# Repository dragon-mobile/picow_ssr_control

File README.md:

# picow_ssr_control

<br/>

<br/>

The Raspberry Pi Pico W Solid State Relay Controller is primarily meant to be
used with an open hardware solid state relay PCBs that is being co-developed
alongside this project as part of my Dragon Mobile GitHub organization to make
useful hardware with associated firmware and software for the tiny home, van
life and maker communities.

## Contributing

Contributors are welcome.
Please note that this project has a [Contributor Covenant Code of Conduct].
By participating in this project you agree to abide by its terms.

All intentionally contributed hardware will be considered to be contributed
under the [CERN] license without any additional terms or conditions.

All intentionally contributed code will be considered to be contributed
under a [MIT] license without any additional terms or conditions.
Please include your information in a comment on all code files for the copyright
etc.

All intentionally contributed documentation, CAD files and libraries, footprints,
artwork or non-code text like this README etc. will be considered to be
contributed under the same [CC-BY-SA] license without any additional terms or
conditions.

Pull requests are always welcome. For major changes, please open an issue first
to discuss what you would like to change.
Please make sure to update or add tests as appropriate for all software changes.

## Licenses

<br/>

All hardware is licensed under the

  * [CERN] - CERN-OHL-W-2.0
  
You can find a copy of the CERN Open Hardware License - Weakly-reciprocal v2.0
in the [LICENSE-CERN-OHL-W-2] file and the how-to guide in the
[CERN-HOWTO_GUIDE] file.

All code is licensed under the

  * [MIT] - MIT License

You can find a copy of the license in the [LICENSE-MIT] file.

All documentation like this README is licensed under the Creative Commons
Attribution-ShareAlike 4.0 International License (CC-BY-SA).

All original CAD files and libraries, footprints, and artwork are also licensed
under the
Creative Commons Attribution-ShareAlike 4.0 International License (CC-BY-SA).
You can find a copy of the [CC-BY-SA] license in the [LICENSE-CC-BY-SA] file.

If after reading the above license files, how-tos, and related FAQs on the
linked license sites on how they apply to the project please either open an
issue or contact me (Michael Cummings) via my Github email and I will try
to guided you through my understanding of how it works.

[CC-BY-SA]: http://creativecommons.org/licenses/by-sa/4.0/
[CERN]: https://ohwr.org/project/cernohl/wikis/Documents/CERN-OHL-version-2
[CERN-HOWTO_GUIDE]: docs/cern_ohl_w_v2_howto.pdf
[Contributor Covenant Code of Conduct]: CODE_OF_CONDUCT.md 
[LICENSE-CC-BY-SA]: LICENSE-CC-BY-SA
[LICENSE-CERN-OHL-W-2]: CERN-OHL-W-2
[LICENSE-MIT]: LICENSE-MIT
[MIT]: https://opensource.org/licenses/MIT

<hr>
Copyright &copy; 2022-2023, Michael Cummings<br/>

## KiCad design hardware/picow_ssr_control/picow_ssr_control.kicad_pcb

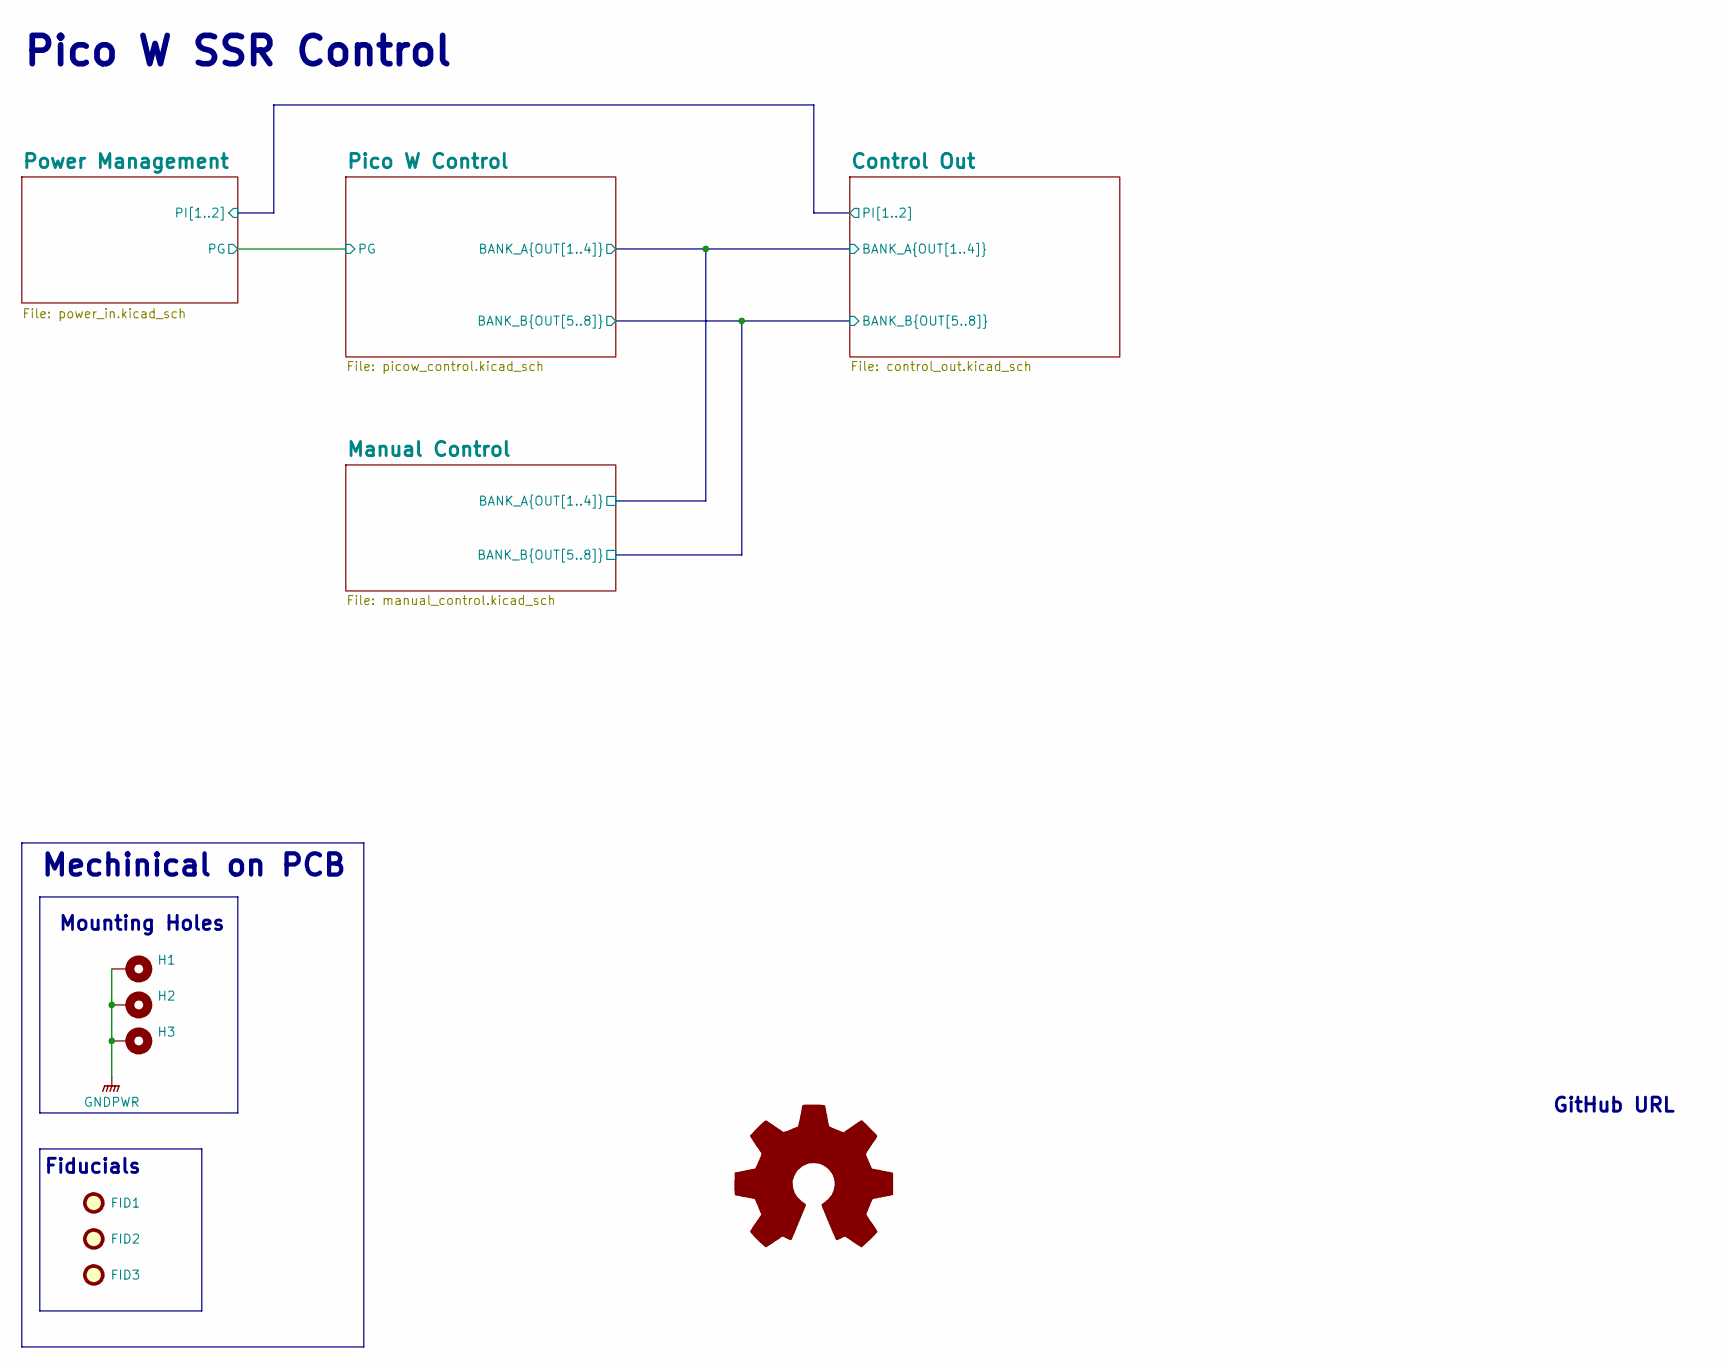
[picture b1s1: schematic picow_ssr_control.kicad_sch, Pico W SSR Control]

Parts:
FID1, FID2, FID3: Fiducial; Fiducial_0.5mm_Mask1mm
H1, H2, H3: MountingHole_Pad; MountingHole_3.2mm_M3_Pad_Via

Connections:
GNDPWR: H1.1, H2.1, H3.1; also elsewhere on the board

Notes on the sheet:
${TITLE}
Mounting Holes
GitHub URL
Mechinical on PCB
Fiducials

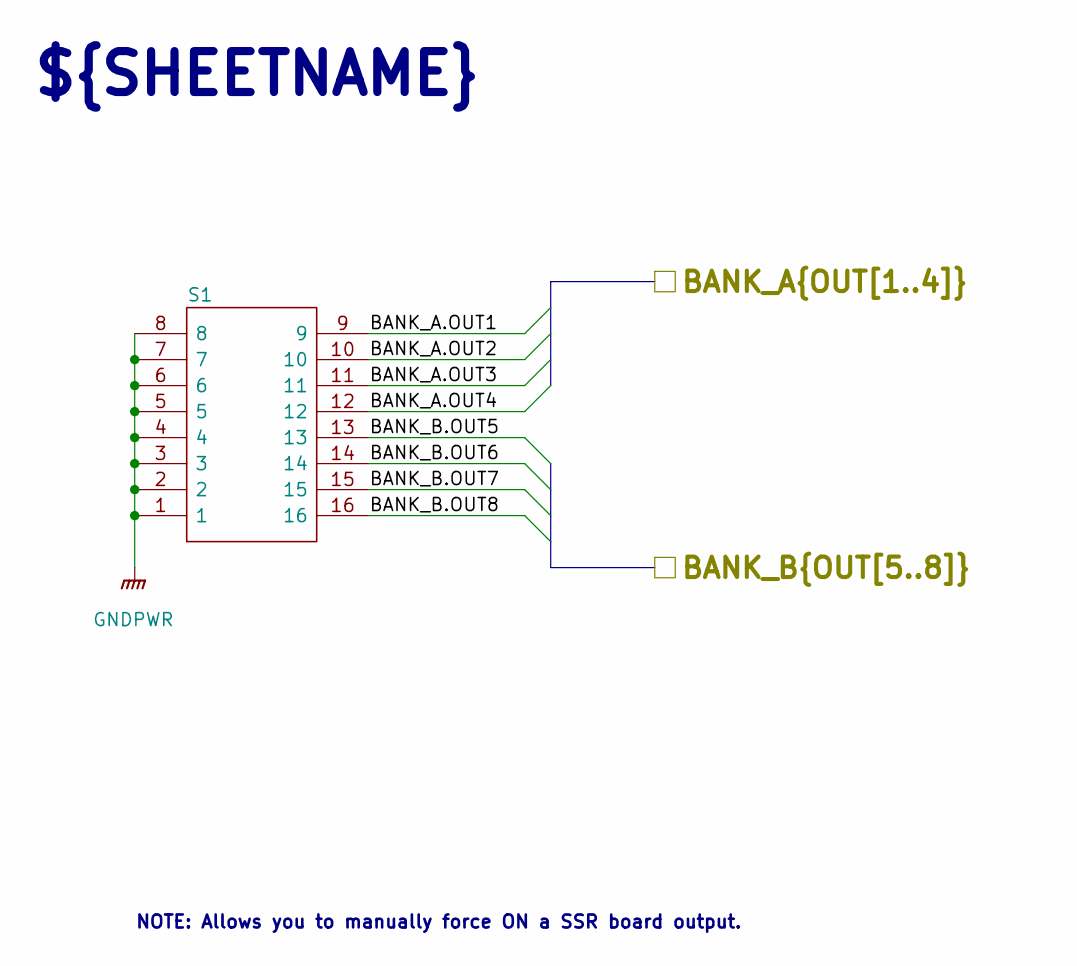
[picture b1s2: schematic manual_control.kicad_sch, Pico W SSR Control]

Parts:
S1: 193-8MS; 1938MS; Mouser Part Number 774-1938MS

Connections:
/Control Out/BANK_A.OUT1: S1.9; also elsewhere on the board
/Control Out/BANK_A.OUT2: S1.10; also elsewhere on the board
/Control Out/BANK_A.OUT3: S1.11; also elsewhere on the board
/Control Out/BANK_A.OUT4: S1.12; also elsewhere on the board
/Control Out/BANK_B.OUT5: S1.13; also elsewhere on the board
/Control Out/BANK_B.OUT6: S1.14; also elsewhere on the board
/Control Out/BANK_B.OUT7: S1.15; also elsewhere on the board
/Control Out/BANK_B.OUT8: S1.16; also elsewhere on the board
GNDPWR: S1.1, S1.2, S1.3, S1.4, S1.5, S1.6, S1.7, S1.8; also elsewhere on the board

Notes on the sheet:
${SHEETNAME}
NOTE: Allows you to manually force ON a SSR board output.

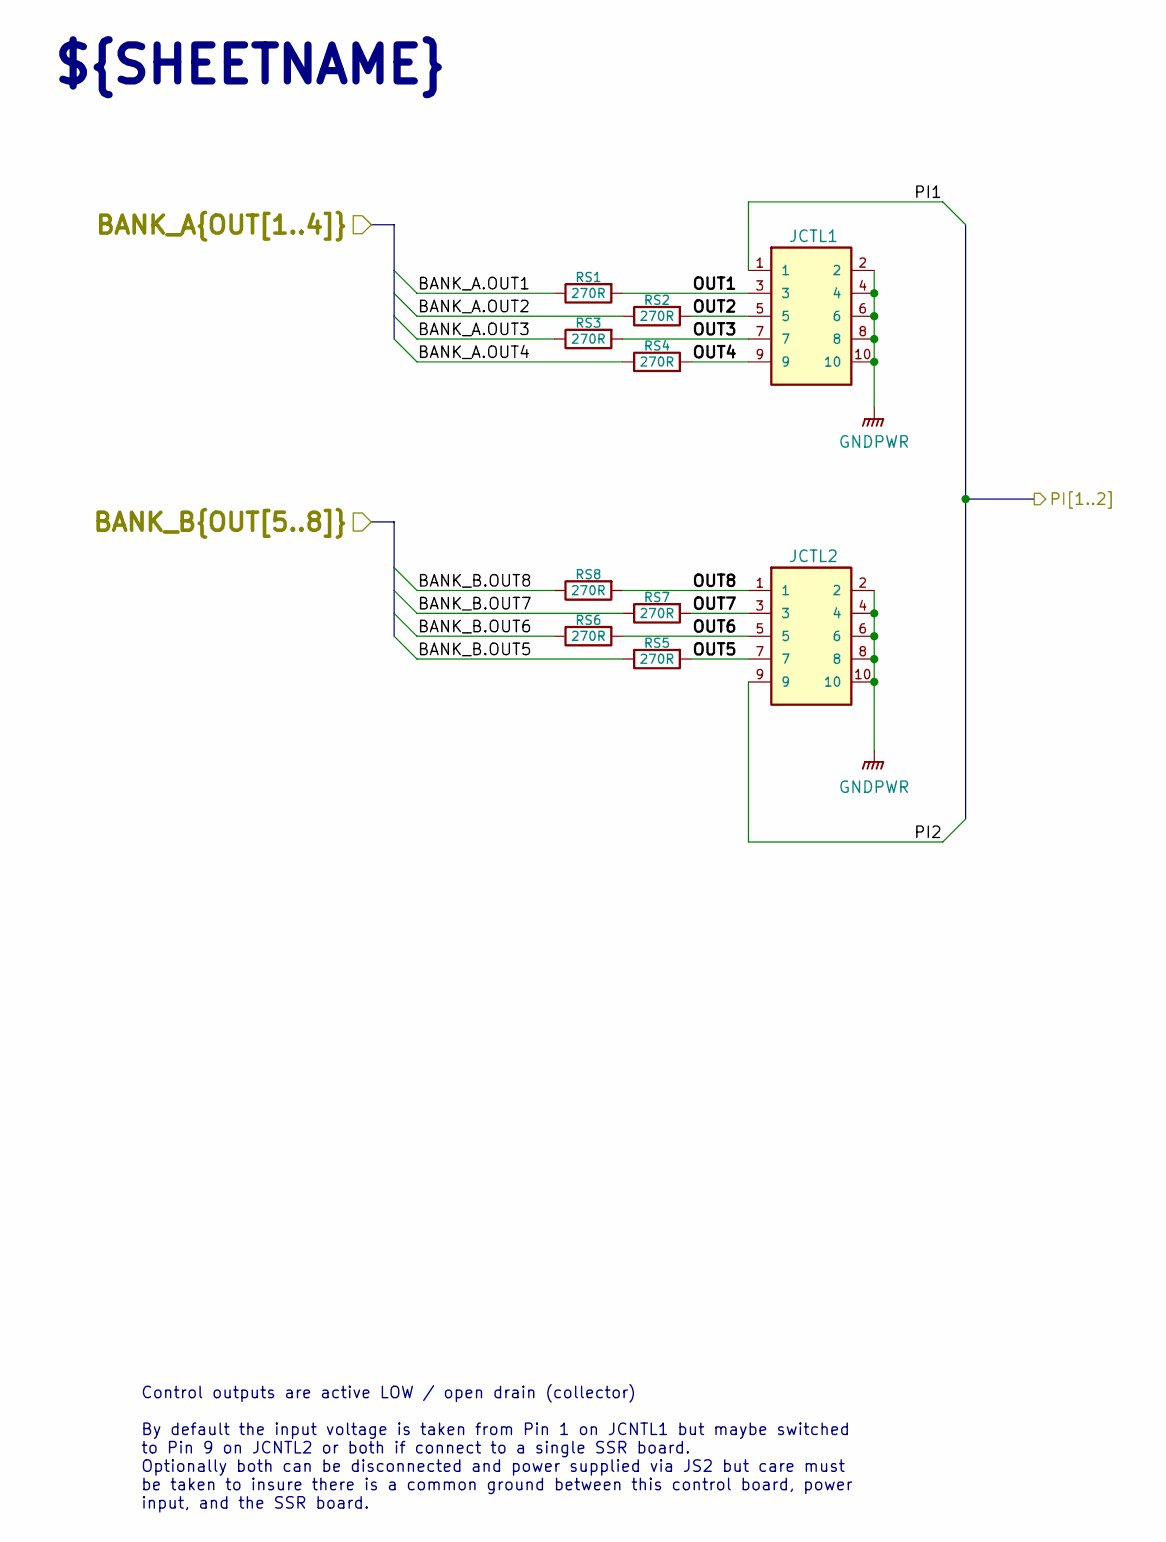
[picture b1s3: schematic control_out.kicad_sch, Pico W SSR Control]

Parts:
JCTL1, JCTL2: SHF-105-01-L-D-RA; SAMTEC_SHF-105-01-L-D-RA; Mouser Part Number 200-SHF10501LDRATR
RS1, RS2, RS3, RS4, RS5, RS6, RS7, RS8: 270R; R_0603_1608Metric; Mouser Part Number 755-SDR03EZPJ271

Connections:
/Control Out/BANK_A.OUT1: RS1.1; also elsewhere on the board
/Control Out/BANK_A.OUT2: RS2.1; also elsewhere on the board
/Control Out/BANK_A.OUT3: RS3.1; also elsewhere on the board
/Control Out/BANK_A.OUT4: RS4.1; also elsewhere on the board
/Control Out/BANK_B.OUT5: RS5.1; also elsewhere on the board
/Control Out/BANK_B.OUT6: RS6.1; also elsewhere on the board
/Control Out/BANK_B.OUT7: RS7.1; also elsewhere on the board
/Control Out/BANK_B.OUT8: RS8.1; also elsewhere on the board
/Control Out/OUT1: JCTL1.3, RS1.2
/Control Out/OUT2: JCTL1.5, RS2.2
/Control Out/OUT3: JCTL1.7, RS3.2
/Control Out/OUT4: JCTL1.9, RS4.2
/Control Out/OUT5: JCTL2.7, RS5.2
/Control Out/OUT6: JCTL2.5, RS6.2
/Control Out/OUT7: JCTL2.3, RS7.2
/Control Out/OUT8: JCTL2.1, RS8.2
/Control Out/PI1: JCTL1.1; also elsewhere on the board
/Control Out/PI2: JCTL2.9; also elsewhere on the board
GNDPWR: JCTL1.2, JCTL1.4, JCTL1.6, JCTL1.8, JCTL1.10, JCTL2.2, JCTL2.4, JCTL2.6, JCTL2.8, JCTL2.10; also elsewhere on the board

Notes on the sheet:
Control outputs are active LOW / open drain (collector) By default the input voltage is taken from Pin 1 on JCNTL1 but maybe switched to Pin 9 on JCNTL2 or both if connect to a single SSR board. Optionally both can be disconnected and power supplied via JS2 but care must be taken to insure there is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
${SHEETNAME}

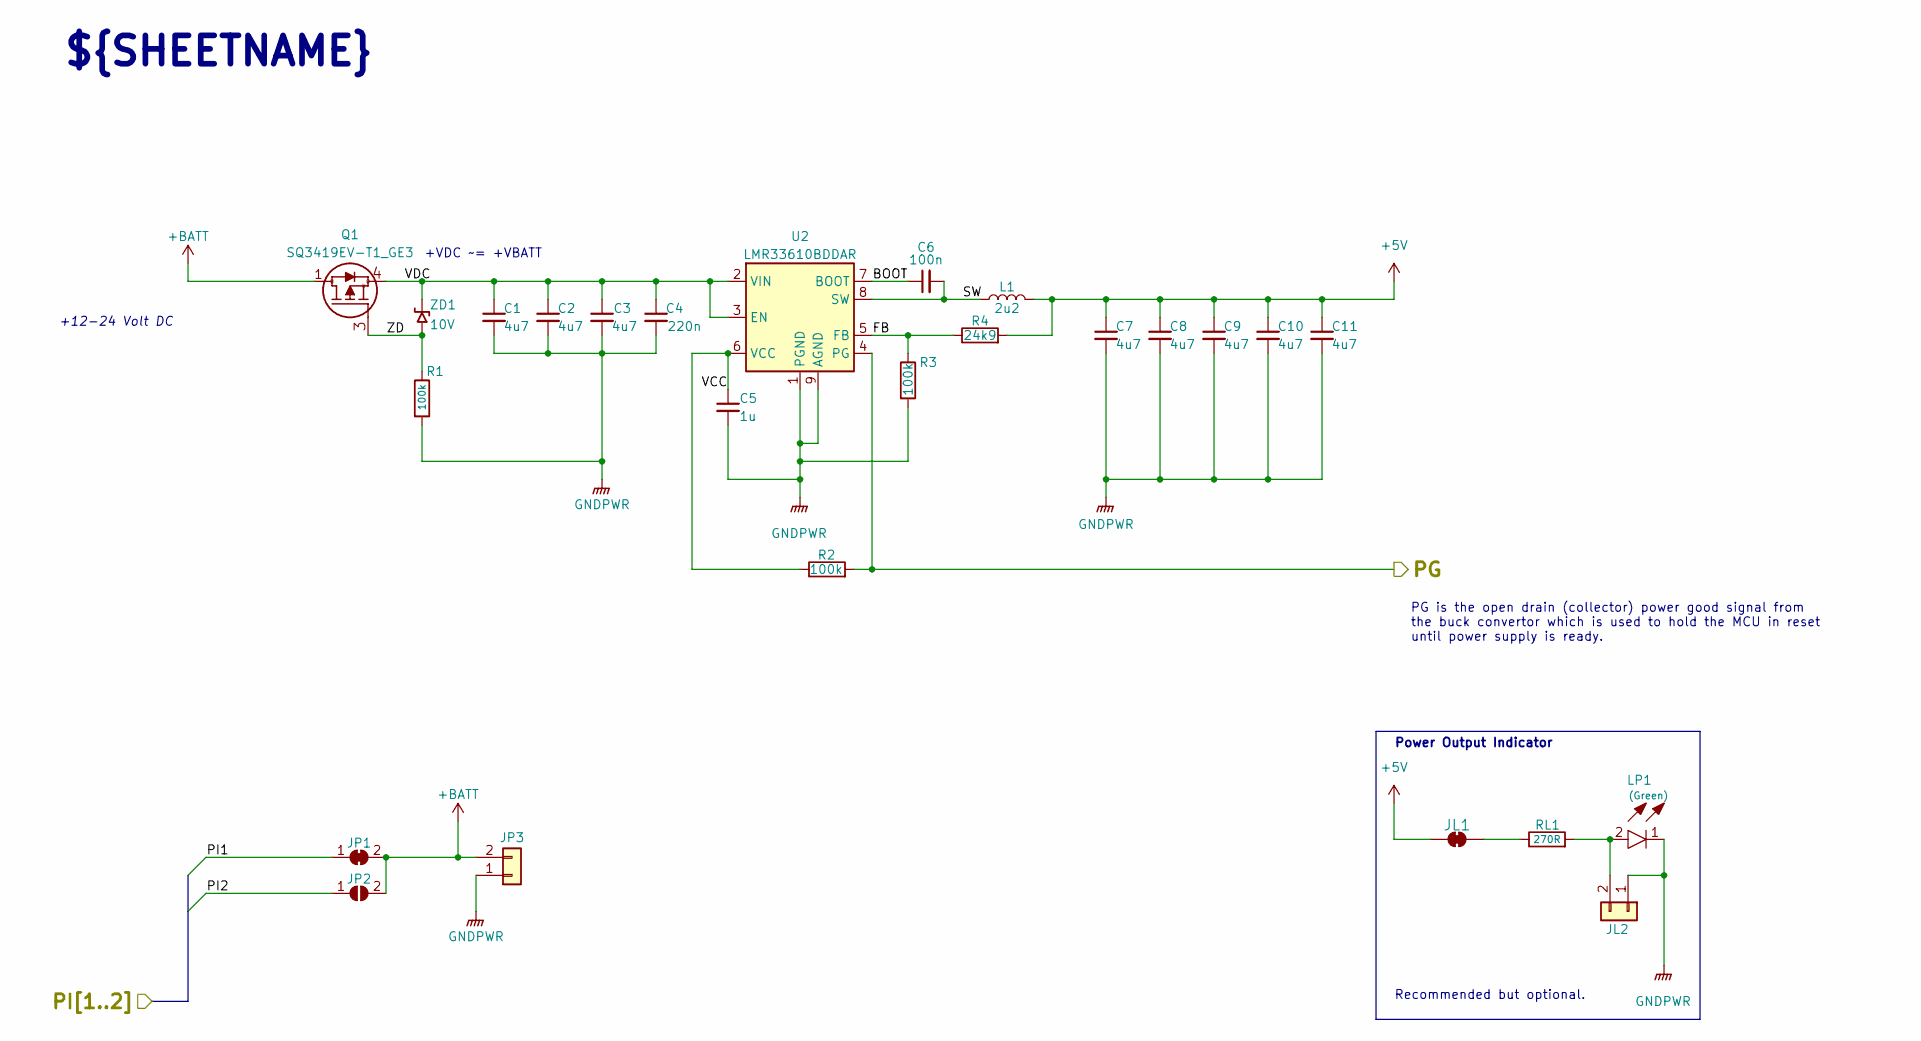
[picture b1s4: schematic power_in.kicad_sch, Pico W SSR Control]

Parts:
C1, C2, C3, C7, C8, C9, C10, C11: 4u7; C_0805_2012Metric; Mouser Part Number 810-CGA4J1X7R1H475K1
C4: 220n; C_0603_1608Metric; Mouser Part Number 810-CGA3E3X7R1H224K
C5: 1u; C_0603_1608Metric; Mouser Part Number 810-CGA3E3X5R1H105K
C6: 100n; C_0603_1608Metric; Mouser Part Number 810-CGA3E2X7R1H104K
JL1: SolderJumper_2_Bridged; SolderJumper-2_P1.3mm_Bridged_RoundedPad1.0x1.5mm
JL2: Conn_01x02; PinHeader_1x02_P1.00mm_Vertical
JP1: SolderJumper_2_Bridged; SolderJumper-2_P1.3mm_Bridged_RoundedPad1.0x1.5mm
JP2: SolderJumper_2_Open; SolderJumper-2_P1.3mm_Open_RoundedPad1.0x1.5mm
JP3: Conn_01x02; PinHeader_1x02_P1.00mm_Vertical
L1: 2u2; L_1008_2520Metric; Mouser Part Number 810-TFM252012ALVA2R2
LP1: LTST-C190KGKT; LEDC1608X80N; Mouser Part Number 859-LTST-C190KGKT
Q1: SQ3419EV-T1_GE3; SOT95P284X110-6N; Mouser Part Number 78-SQ3419EV-T1_GE3
R1, R2, R3: 100k; R_0603_1608Metric; Mouser Part Number 667-ERJ-PA3F1003V
R4: 24k9; R_0603_1608Metric; Mouser Part Number 667-ERJ-PA3F2492V
RL1: 270R; R_0603_1608Metric; Mouser Part Number 755-SDR03EZPJ271
U2: LMR33610BDDAR; Texas_HSOP-8-1EP_3.9x4.9mm_P1.27mm_ThermalVias; Mouser Part Number 595-LMR33610BDDAR
ZD1: 10V; D_0805_2012Metric; Mouser Part Number 821-BZY55B10RBG

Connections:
+5V: C7.1, C8.1, C9.1, C10.1, C11.1, JL1.1 (A), L1.2, R4.2; also elsewhere on the board
+BATT: JP1.2 (B), JP2.2 (B), JP3.2, Q1.1 (D), Q1.2 (D), Q1.5 (D), Q1.6 (D)
/Control Out/PI1: JP1.1 (A); also elsewhere on the board
/Control Out/PI2: JP2.1 (A); also elsewhere on the board
/Pico W Control/PG: R2.2, U2.4 (PG); also elsewhere on the board
/Power Management/BOOT: C6.1, U2.7 (BOOT)
/Power Management/FB: R3.1, R4.1, U2.5 (FB)
/Power Management/SW: C6.2, L1.1, U2.8 (SW)
/Power Management/VCC: C5.1, R2.1, U2.6 (VCC)
/Power Management/VDC: C1.1, C2.1, C3.1, C4.1, Q1.4 (S), U2.2 (VIN), U2.3 (EN), ZD1.1
/Power Management/ZD: Q1.3 (G), R1.1, ZD1.2
GNDPWR: C1.2, C2.2, C3.2, C4.2, C5.2, C7.2, C8.2, C9.2, C10.2, C11.2, JL2.1, JP3.1, LP1.1, R1.2, R3.2, U2.1 (PGND), U2.9 (AGND); also elsewhere on the board
unnamed: JL1.2 (B), RL1.1
unnamed: JL2.2, LP1.2, RL1.2

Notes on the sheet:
+VDC ~= +VBATT
+12-24 Volt DC
Recommended but optional.
Power Output Indicator
PG is the open drain (collector) power good signal from the buck convertor which is used to hold the MCU in reset until power supply is ready.
${SHEETNAME}

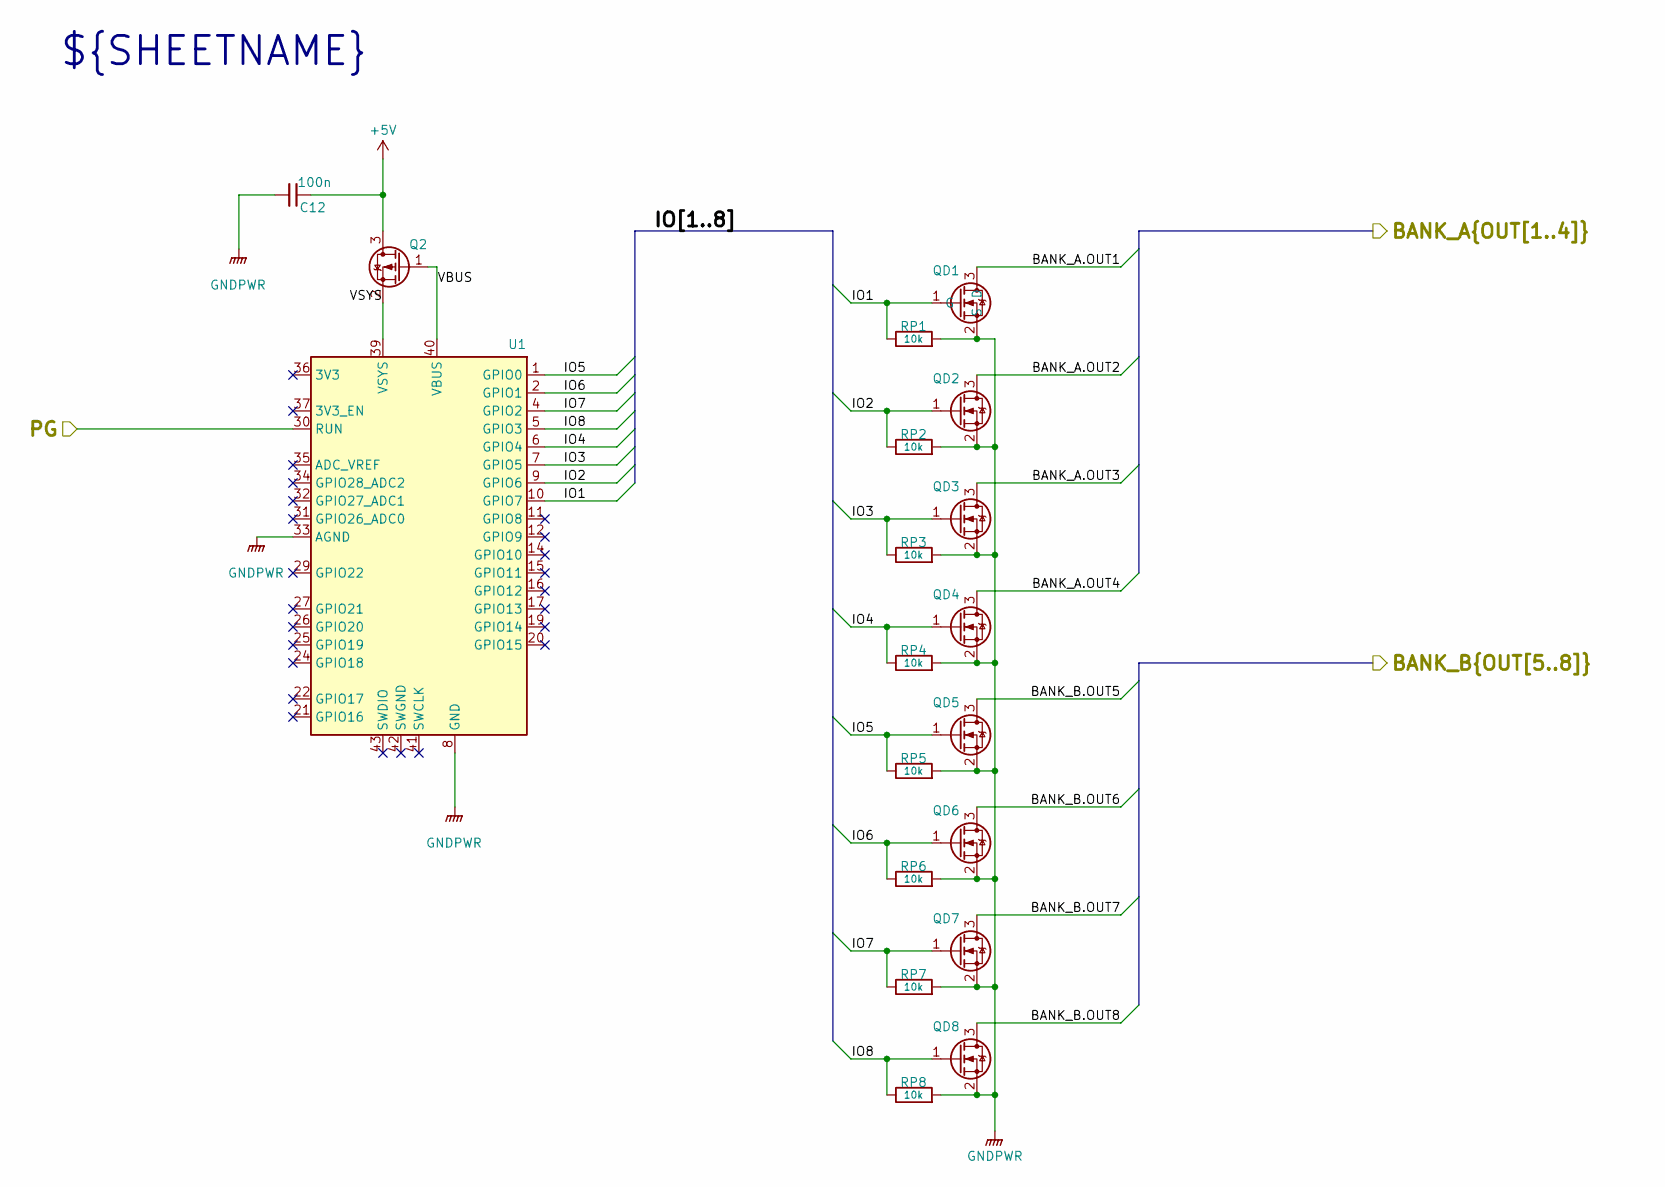
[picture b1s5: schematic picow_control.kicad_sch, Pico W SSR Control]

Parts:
C12: 100n; C_0603_1608Metric; Mouser Part Number 810-CGA3E2X7R1H104K
Q2: DMG2305UX-7; SOT-23; Mouser Part Number 621-DMG2305UX-7
QD1, QD2, QD3, QD4, QD5, QD6, QD7, QD8: 2N7002K; 2V7002KT1G; Mouser Part Number 863-2V7002KT1G
RP1, RP2, RP3, RP4, RP5, RP6, RP7, RP8: 10k; R_0603_1608Metric; Mouser Part Number 755-SDR03EZPJ103
U1: RaspberryPi-PicoW; Raspberry_Pi_Pico_THT

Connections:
+5V: C12.1, Q2.3 (D); also elsewhere on the board
/Control Out/BANK_A.OUT1: QD1.3 (D); also elsewhere on the board
/Control Out/BANK_A.OUT2: QD2.3 (D); also elsewhere on the board
/Control Out/BANK_A.OUT3: QD3.3 (D); also elsewhere on the board
/Control Out/BANK_A.OUT4: QD4.3 (D); also elsewhere on the board
/Control Out/BANK_B.OUT5: QD5.3 (D); also elsewhere on the board
/Control Out/BANK_B.OUT6: QD6.3 (D); also elsewhere on the board
/Control Out/BANK_B.OUT7: QD7.3 (D); also elsewhere on the board
/Control Out/BANK_B.OUT8: QD8.3 (D); also elsewhere on the board
/Pico W Control/IO1: QD1.1 (G), RP1.1, U1.10 (GPIO7)
/Pico W Control/IO2: QD2.1 (G), RP2.1, U1.9 (GPIO6)
/Pico W Control/IO3: QD3.1 (G), RP3.1, U1.7 (GPIO5)
/Pico W Control/IO4: QD4.1 (G), RP4.1, U1.6 (GPIO4)
/Pico W Control/IO5: QD5.1 (G), RP5.1, U1.1 (GPIO0)
/Pico W Control/IO6: QD6.1 (G), RP6.1, U1.2 (GPIO1)
/Pico W Control/IO7: QD7.1 (G), RP7.1, U1.4 (GPIO2)
/Pico W Control/IO8: QD8.1 (G), RP8.1, U1.5 (GPIO3)
/Pico W Control/PG: U1.30 (RUN); also elsewhere on the board
/Pico W Control/VBUS: Q2.1 (G), U1.40 (VBUS)
/Pico W Control/VSYS: Q2.2 (S), U1.39 (VSYS)
GNDPWR: C12.2, QD1.2 (S), QD2.2 (S), QD3.2 (S), QD4.2 (S), QD5.2 (S), QD6.2 (S), QD7.2 (S), QD8.2 (S), RP1.2, RP2.2, RP3.2, RP4.2, RP5.2, RP6.2, RP7.2, RP8.2, U1.3 (GND), U1.8 (GND), U1.13 (GND), U1.18 (GND), U1.23 (GND), U1.28 (GND), U1.33 (AGND), U1.38 (GND); also elsewhere on the board

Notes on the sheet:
${SHEETNAME}

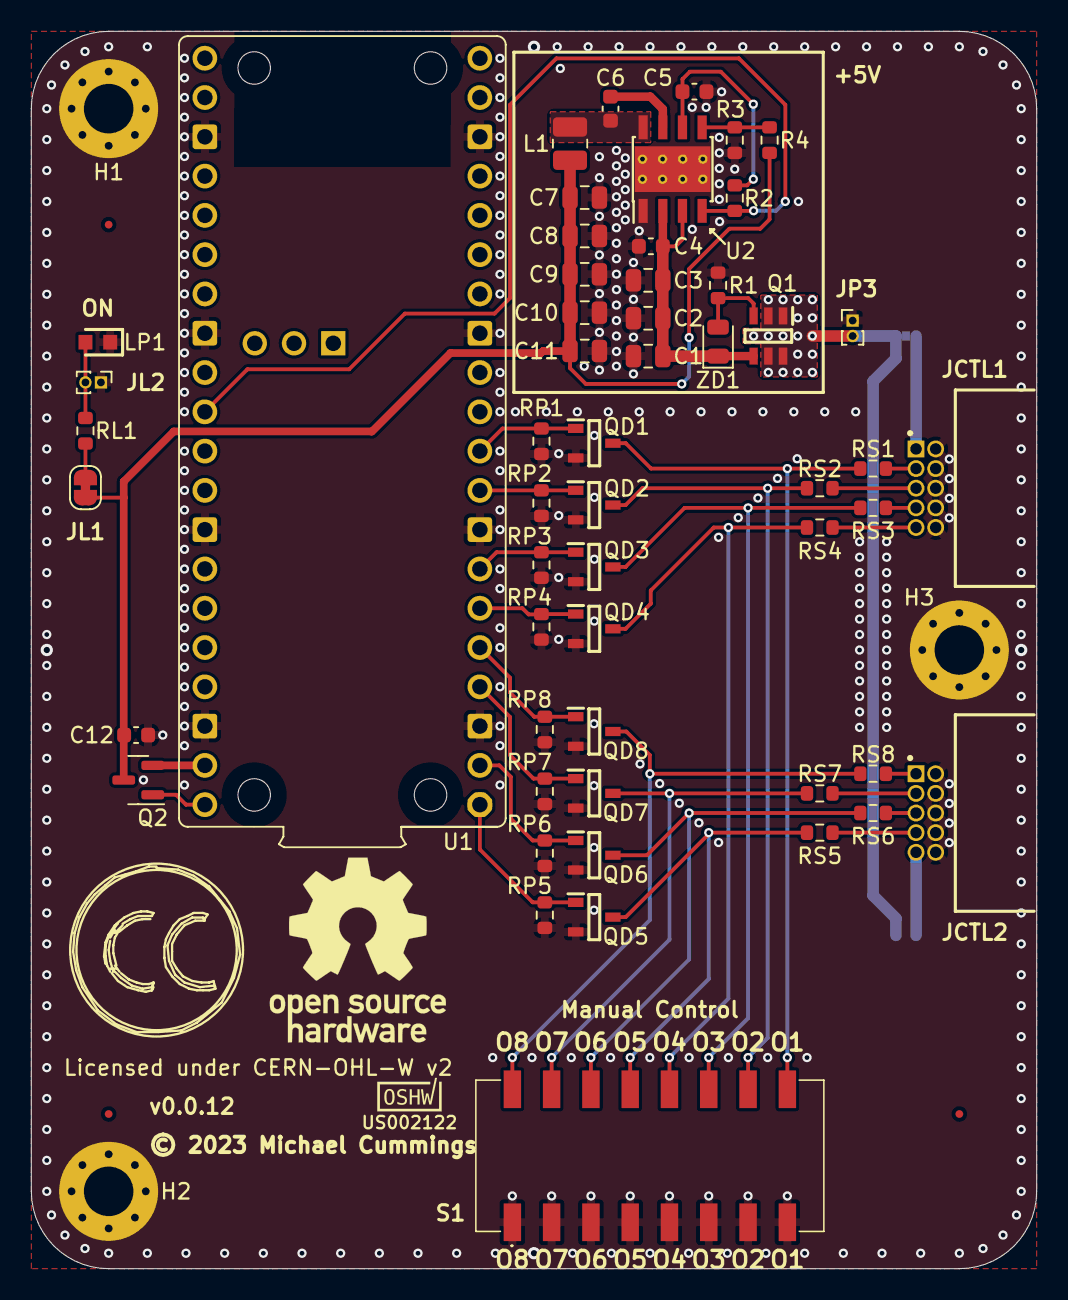
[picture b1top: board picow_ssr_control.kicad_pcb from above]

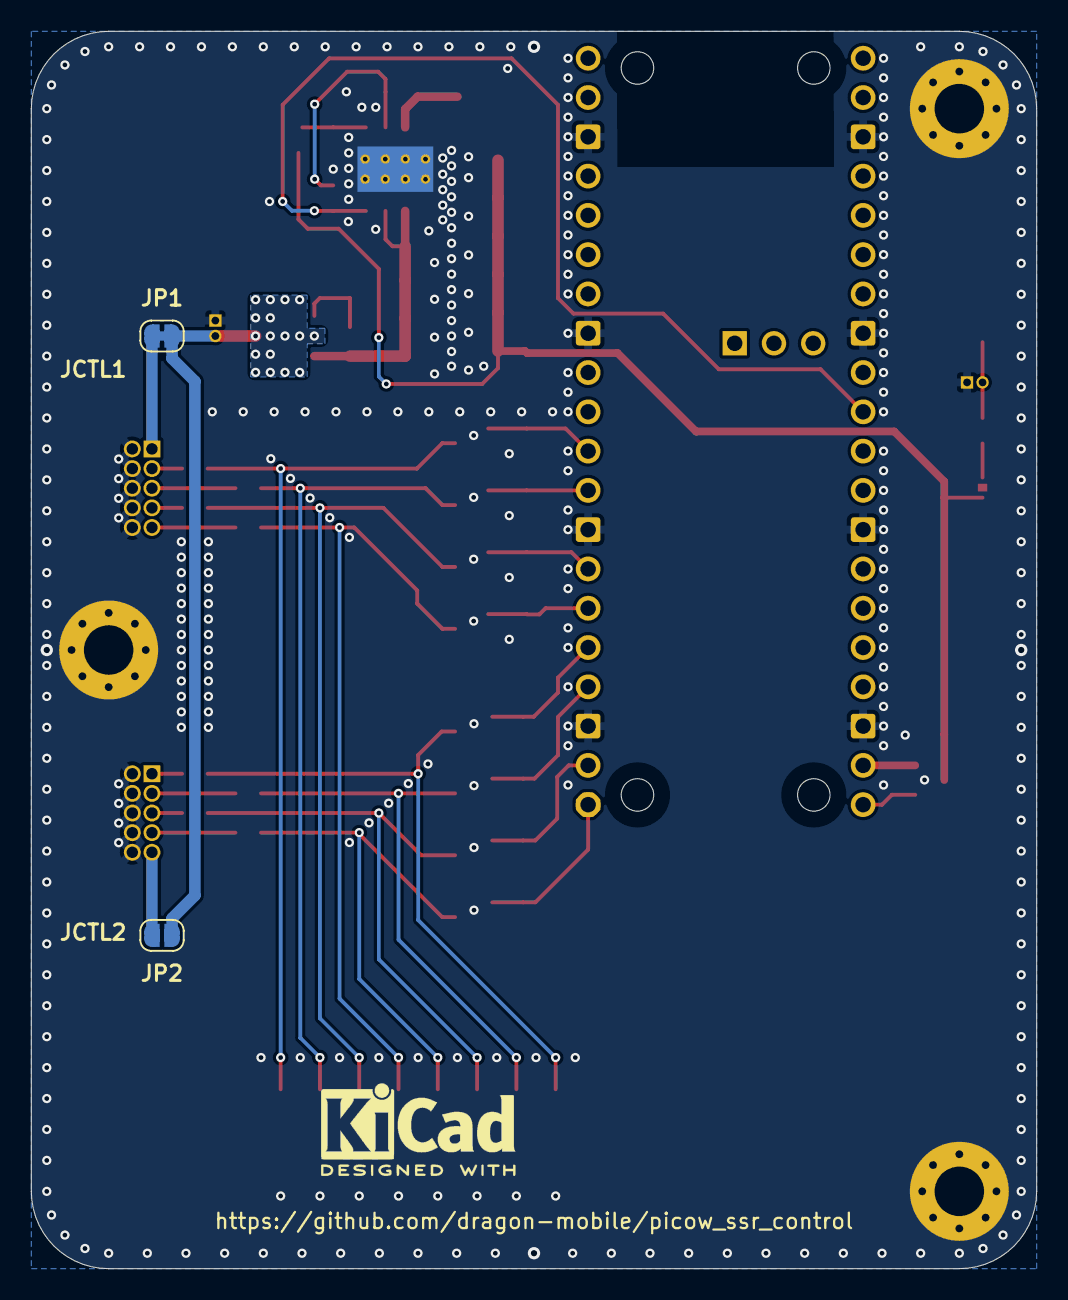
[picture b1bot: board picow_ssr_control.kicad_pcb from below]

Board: 2 copper layers, 65.0 x 80.0 mm, 66 parts (3 on the bottom side), 40 nets.

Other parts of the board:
JCNTL1_Label: JCNTL1_Label
JCNTL2_Label: JCNTL2_Label
OSHW_Mono_0.1_Scale: ${COMMENT5}; OSHW_Mono_0.1_Scale
REF_KiCAD: KiCad-Logo2_5mm_SilkScreen

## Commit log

2022-07-22 Setup project structure
2022-07-23 Updated README.md and added correct license files.
2022-07-26 Added project symbols, footprints etc.
2022-07-26 Added Copyright and logos etc.
2022-07-27 Added Updated symbol, footprint, 3d model for zener diode
2022-07-27 Fixed Code of Conduct link in README.md
2022-07-27 Adding first couple badges to README.md
2022-07-27 Try1 to fixed FOSSA Status badge
2022-07-27 Removed FOSSA badge and added license badge
2022-07-27 Adding some additional badges to readme.
2022-07-27 More badges updates to readme.
2022-07-27 More badges updates #2
2022-08-06 Add new Cern licensing info
2022-08-06 Added missing Cern files
2022-08-06 Fixed Cern license link in README
2022-08-06 Fixed Cern license link in README try 2
2022-08-06 Synced up schema and PCB versions and Licensing silkscreening
2022-08-06 Fixed incorrect copyright date on PCB
2022-08-06 Some addition updates to README
2022-08-06 Added CERN license to shield icon in README
2022-12-08 WIP control connector changes v0.0.7
2022-12-22 Replaced un-obtainable ULN2803 with SMD FETs and updated control connectors
2023-01-02 Misc minor updates after tag
2023-01-03 Vertical Pico, Moved connectors, and draft production files
2023-01-12 Updated copyright in README.md
2023-01-13 Added front & back PCB pics and start of desc. to README.md
2023-01-24 Added pulldowns to driver FETs and realigned control connectors and other components
2023-01-28 Changed schematic to hierarchical style with mutliple sheets
2023-02-05 Updated schemas
2023-02-08 Power supply changes plus misc.
2023-02-13 Pre KiCad 7.0.0 WIP
2023-02-13 Added share_components submodule
2023-03-13 Commit before trying changes to power system
2023-03-16 Commit before removing git submodule
2023-03-16 Commit before removing git submodule try #2
2023-03-16 Commit removing git submodule

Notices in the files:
README.md:
https://img.shields.io/static/v1?label=license&message=CERN-OHL-W-2.0%20%2F%20MIT%20%2F%20CC-BY-SA-4.0&color=orange
CC BY-SA 4.0
hardware/picow_ssr_control/control_out.kicad_sch:
Hardware License: CERN-OHL-W
https://creativecommons.org/licenses/by-sa/4.0
License: CC By SA 4.0
hardware/picow_ssr_control/picow_ssr_control.kicad_pcb:
© 2023 ${COMPANY}
Licensed under CERN-OHL-W v2
